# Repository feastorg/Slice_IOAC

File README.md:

# Slice Template

Mixed analog and digital I/O slice with protected inputs, buffered outputs, and basic control interfaces.

Template for creating BREAD slices. Features Arduino Nano, small dimensions (70x100mm), 2 layers, and this is the second revision (TEMP_NANO_S2L-r2).

## Introduction

[Short introduction on the project.]

## Usage

[Explain how to use the project. Include examples and screenshots if applicable.]

## Documentation

Please refer to the [docs](/docs) for more info.

---

<div align="center">
  
</div>

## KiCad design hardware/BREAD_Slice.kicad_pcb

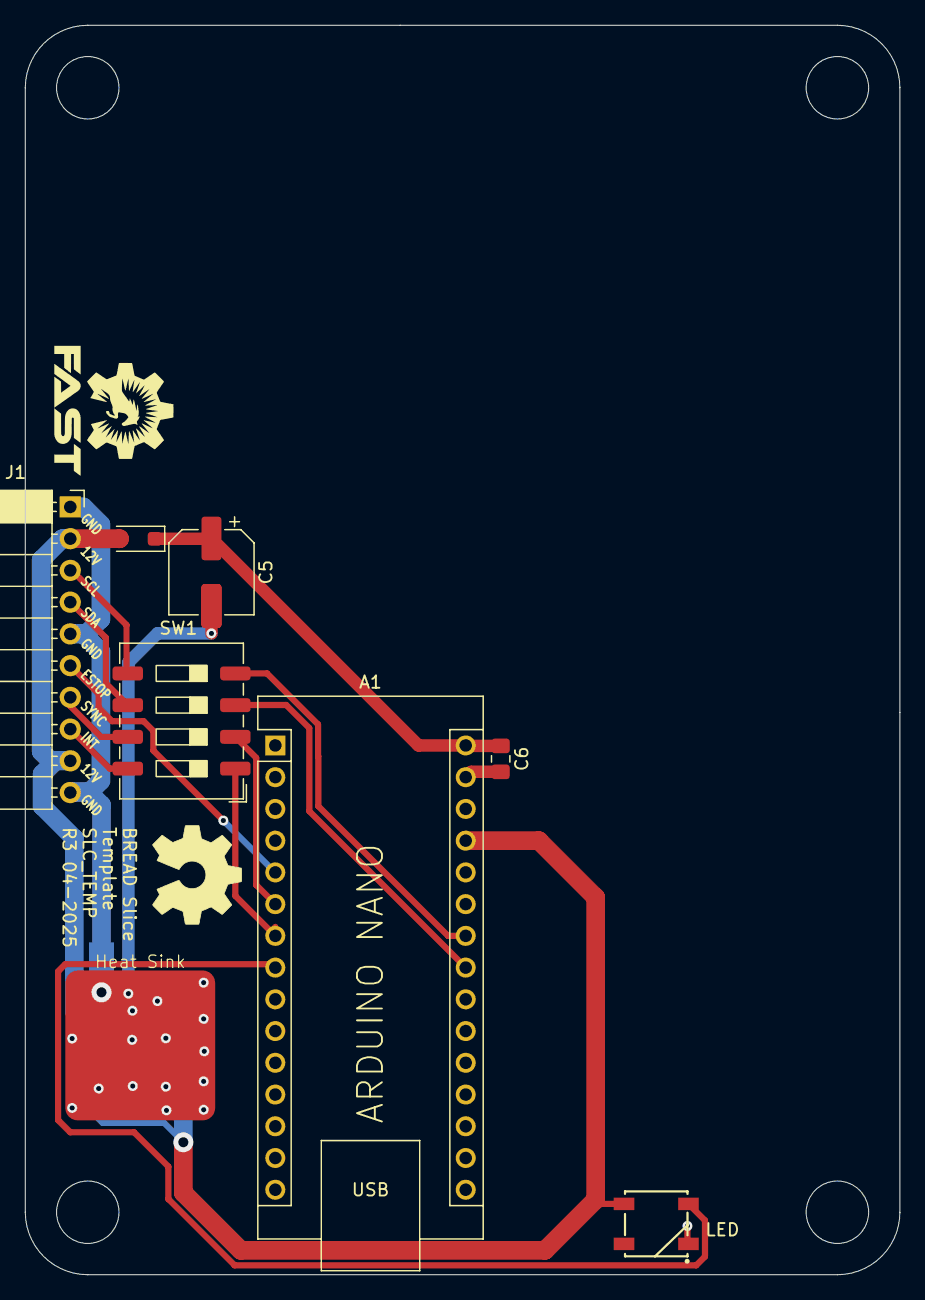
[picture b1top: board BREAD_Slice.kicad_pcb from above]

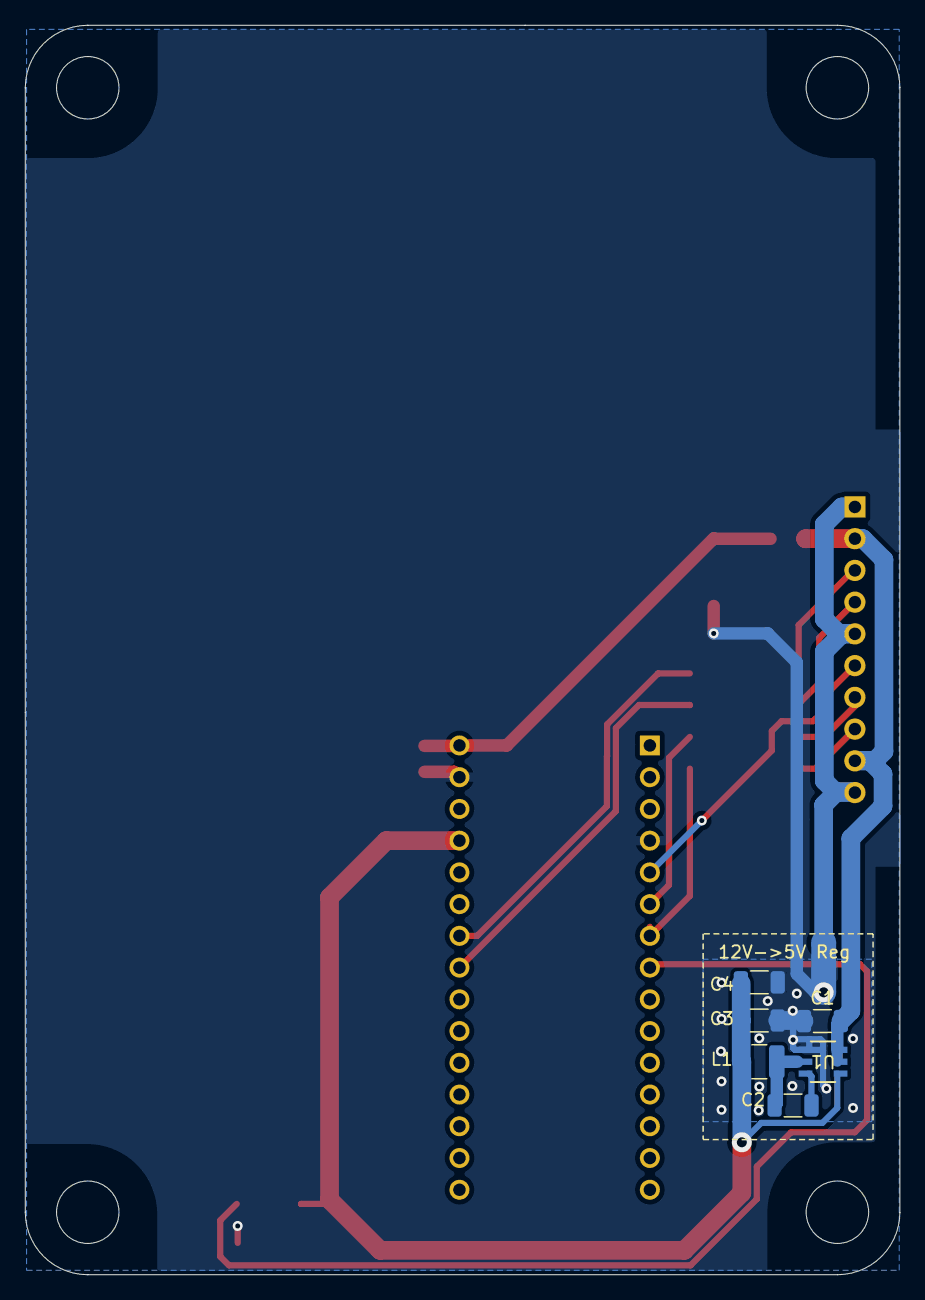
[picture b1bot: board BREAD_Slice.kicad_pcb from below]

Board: 2 copper layers, 70.0 x 100.0 mm, 20 parts (7 on the bottom side), 17 nets.

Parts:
A1: Arduino_Nano_v3.x; Arduino_Nano_Headers
C1: 10u; C_1206_3216Metric
C2: 100nF; C_1206_3216Metric
C3, C4: 22uF; C_1206_3216Metric
C5: 47u 25V; CP_Elec_6.3x7.7
C6: 0.1u; C_0805_2012Metric_Pad1.18x1.45mm_HandSolder
D1: 1N4007; D_SOD-123F
D2: WS2812B_5050; WS2812-5050-4PIN
H1, H2, H3, H4: MountingHole; MountingHole_5mm
HS1: Heatsink_Pad; Thermal_Pad
J1: Conn_01x10_Socket; PinSocket_1x10_P2.54mm_Horizontal
L1: 4.7uH; L_1210_3225Metric
NT1: NetTie_2; NetTie-2_SMD_Pad2.0mm
Ref**: Val**; OSHW_Logo_8mm
SW1: SW_DIP_x04; SW_DIP_SPSTx04_Slide_9.78x12.34mm_W8.61mm_P2.54mm
U1: AP63205; SOIC_05WU-7_DIO-M

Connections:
+5V: A1.27 (+5V), C3.2, C4.2, D2.1 (VDD), L1.2, U1.1 (FB)
+12V: C1.2, D1.2 (A), J1.2, J1.9, U1.2 (EN), U1.3 (VIN)
/slice_template/ESTOP: A1.5 (D2), J1.6
/slice_template/I2C_CLK: J1.3, SW1.5
/slice_template/I2C_CLK/A5: A1.24 (A5), SW1.4
/slice_template/I2C_DAT: J1.4, SW1.6
/slice_template/I2C_DAT/A4: A1.23 (A4), SW1.3
/slice_template/INT: J1.8, SW1.8
/slice_template/INT/CAN_{CS}: A1.7 (D4), SW1.1
/slice_template/LED: A1.8 (D5), D2.4 (DIN)
/slice_template/SYNC: J1.7, SW1.7
/slice_template/SYNC/CAN_{INT}: A1.6 (D3), SW1.2
/slice_template/VIN: A1.30 (VIN), C5.1, C6.1, D1.1 (K)
GND: A1.4 (GND), A1.29 (GND), C1.1, C3.1, C4.1, C5.2, C6.2, D2.3 (VSS), HS1.1, NT1.1, U1.4 (GND)
GNDPWR: J1.1, J1.5, J1.10, NT1.2
unnamed: C2.2, U1.6 (BST)
unnamed: C2.1, L1.1, U1.5 (SW)

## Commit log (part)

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2025-09-28 📄 KiBot index + board renders (auto)
2025-09-28 add plan doc and disable actions for now
2026-04-20 refactor: org casing rename from 'FEASTorg' to 'feastorg'
2026-05-24 Add slice.yaml manifest (schema v1.0)
2026-05-24 Add TODO.md with pipeline status
2026-05-24 chore: desc. to readme
2026-05-24 Standardize TODO.md with Pass 1/Pass 2 structure
